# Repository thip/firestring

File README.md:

# FireString

An RP2040-based LED fire simulation controller that drives WS2812B NeoPixel strings to recreate the look of a glowing fireplace.

Full writeup: [davidcapper.dev/posts/fire-string](https://davidcapper.dev/posts/fire-string)

Finished units available at [hortus.dev/products/fire-string](https://hortus.dev/products/fire-string).

## How it works

The simulation is built on three physical concepts:

- **Black-body radiation** — pixel temperatures are mapped to a colour gradient from red (cool) through orange/yellow to white (hot).
- **Heat decay** — each pixel loses a proportion of its heat every frame, fading from bright to dark over time.
- **Thermal diffusion** — pixels transfer heat to neighbours proportionally to temperature difference, so heat spreads naturally through the string.

On top of this, a **fuel system** adds gradual brightness ramps (fuel converts to heat via a burn rate), and **temperature-dependent curves** make cool pixels decay slowly and reignite easily while hot pixels shed heat rapidly — mimicking real ember behaviour.

## Firmware

CircuitPython running on the RP2040 with `@micropython.viper` compilation and integer-only maths for performance. Includes a **web-based configurator** (Web Serial API) for real-time parameter tuning and preset management.

## Hardware

Custom 2-layer RP2040 PCB with USB-C, designed in KiCad. Schematic and board layout are in `hardware/`.

## Licence

- **Hardware** — [CC BY-NC-SA 4.0](hardware/LICENSE)
- **Software** — [MIT](Software/LICENSE)

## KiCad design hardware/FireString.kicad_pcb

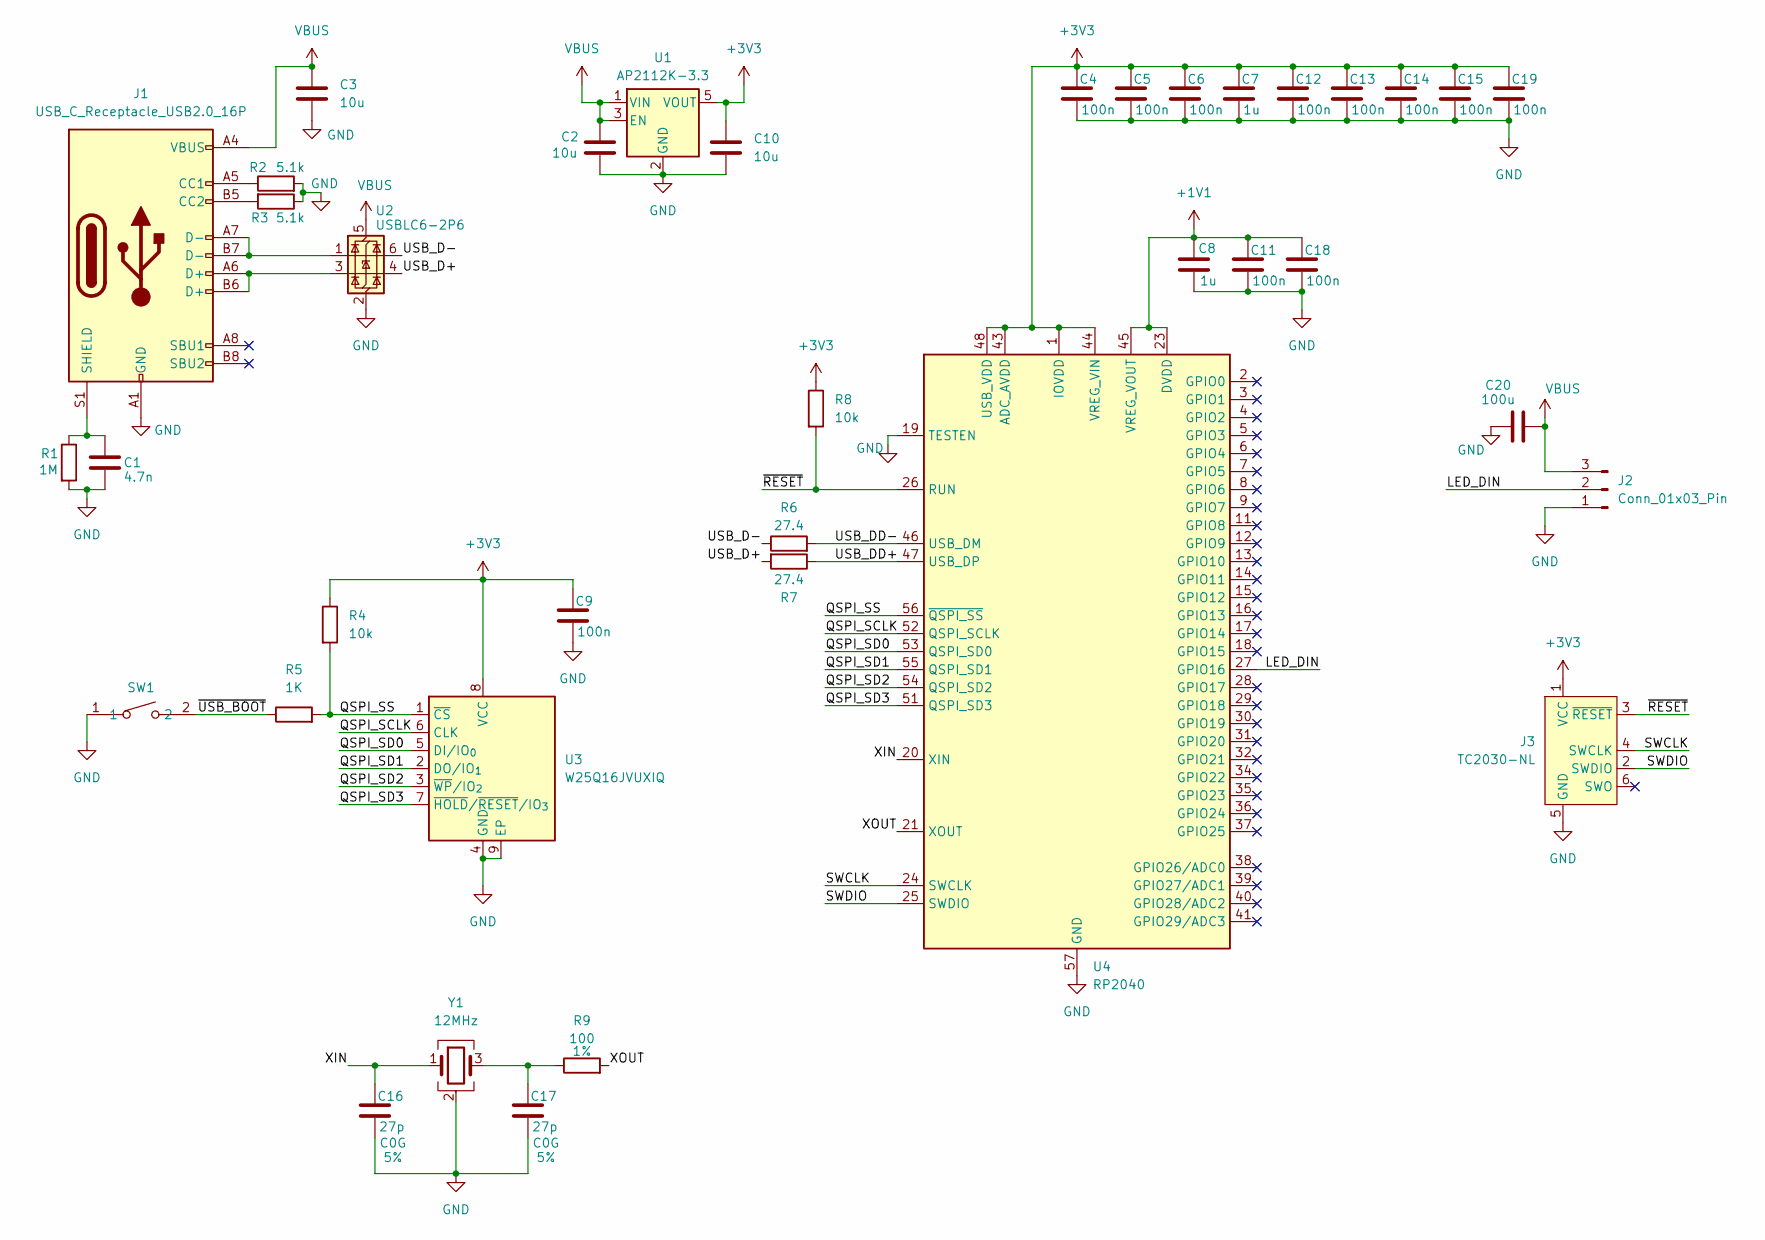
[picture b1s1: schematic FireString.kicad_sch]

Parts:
C1: 4.7n; C_0402_1005Metric
C2, C3, C10: 10u; C_0402_1005Metric
C4, C5, C6, C9, C11, C12, C13, C14, C15, C18, C19: 100n; C_0402_1005Metric
C7, C8: 1u; C_0402_1005Metric
C16, C17: 27p; C_0402_1005Metric; Tolerence 5%
C20: 100u; C_1206_3216Metric
J1: USB_C_Receptacle_USB2.0_16P; USB_C_Receptacle_G-Switch_GT-USB-7010ASV
J2: Conn_01x03_Pin; JST_XH_S3B-XH-A_1x03_P2.50mm_Horizontal
J3: TC2030-NL; Tag-Connect_TC2030-IDC-NL_2x03_P1.27mm_Vertical
R1: 1M; R_0402_1005Metric
R2, R3: 5.1k; R_0402_1005Metric
R4, R8: 10k; R_0402_1005Metric
R5: 1K; R_0402_1005Metric
R6, R7: 27.4; R_0402_1005Metric
R9: 100; R_0402_1005Metric; Tolerence 1%
SW1: SW-SMD_L3.9-W3.0-P4.45
U1: AP2112K-3.3; SOT-23-5
U2: USBLC6-2P6; SOT-666
U3: W25Q16JVUXIQ; USON-8_L3.0-W2.0-P0.50-BL-EP
U4: RP2040; QFN-56-1EP_7x7mm_P0.4mm_EP3.2x3.2mm
Y1: 12MHz; Crystal_SMD_Abracon_ABM8G-4Pin_3.2x2.5mm

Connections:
+1V1: C8.1, C11.1, C18.1, U4.23 (DVDD), U4.45 (VREG_VOUT), U4.50 (DVDD)
+3V3: C4.1, C5.1, C6.1, C7.1, C9.1, C10.1, C12.1, C13.1, C14.1, C15.1, C19.1, J3.1 (VCC), R4.1, R8.1, U1.5 (VOUT), U3.8 (VCC), U4.1 (IOVDD), U4.10 (IOVDD), U4.22 (IOVDD), U4.33 (IOVDD), U4.42 (IOVDD), U4.43 (ADC_AVDD), U4.44 (VREG_VIN), U4.48 (USB_VDD), U4.49 (IOVDD)
/LED_DIN: J2.2, U4.27 (GPIO16)
/QSPI_SCLK: U3.6 (CLK), U4.52 (QSPI_SCLK)
/QSPI_SD0: U3.5 (DI/IO_{0}), U4.53 (QSPI_SD0)
/QSPI_SD1: U3.2 (DO/IO_{1}), U4.55 (QSPI_SD1)
/QSPI_SD2: U3.3 (~WP/IO_{2}), U4.54 (QSPI_SD2)
/QSPI_SD3: U3.7 (~HOLD/~RESET/IO_{3}), U4.51 (QSPI_SD3)
/QSPI_SS: R4.2, R5.2, U3.1 (~CS), U4.56 (~QSPI_SS)
/SWCLK: J3.4 (SWCLK), U4.24 (SWCLK)
/SWDIO: J3.2 (SWDIO), U4.25 (SWDIO)
/USB_D+: R7.2, U2.4 (I/O2)
/USB_D-: R6.1, U2.6 (I/O1)
/USB_DD+: R7.1, U4.47 (USB_DP)
/USB_DD-: R6.2, U4.46 (USB_DM)
/XIN: C16.1, U4.20 (XIN), Y1.1
/XOUT: R9.2, U4.21 (XOUT)
/~RESET: J3.3 (~RESET), R8.2, U4.26 (RUN)
/~USB_BOOT: R5.1, SW1.2
GND: C1.2, C2.2, C3.1, C4.2, C5.2, C6.2, C7.2, C8.2, C9.2, C10.2, C11.2, C12.2, C13.2, C14.2, C15.2, C16.2, C17.2, C18.2, C19.2, C20.1, J1.A1 (GND), J1.A12 (GND), J1.B1 (GND), J1.B12 (GND), J2.1, J3.5 (GND), R1.2, R2.2, R3.1, SW1.1, U1.2 (GND), U2.2 (GND), U3.4 (GND), U3.9 (EP), U4.19 (TESTEN), U4.57 (GND), Y1.2 (G), Y1.4 (G)
unnamed: C17.1, R9.1, Y1.3
unnamed: J1.A5 (CC1), R2.1
unnamed: J1.B5 (CC2), R3.2
unnamed: J1.A6 (D+), J1.B6 (D+), U2.3 (I/O2)
unnamed: J1.A7 (D-), J1.B7 (D-), U2.1 (I/O1)
unnamed: C1.1, J1.S1 (SHIELD), R1.1
VBUS: C2.1, C3.2, C20.2, J1.A4 (VBUS), J1.A9 (VBUS), J1.B4 (VBUS), J1.B9 (VBUS), J2.3, U1.1 (VIN), U1.3 (EN), U2.5 (VBUS)

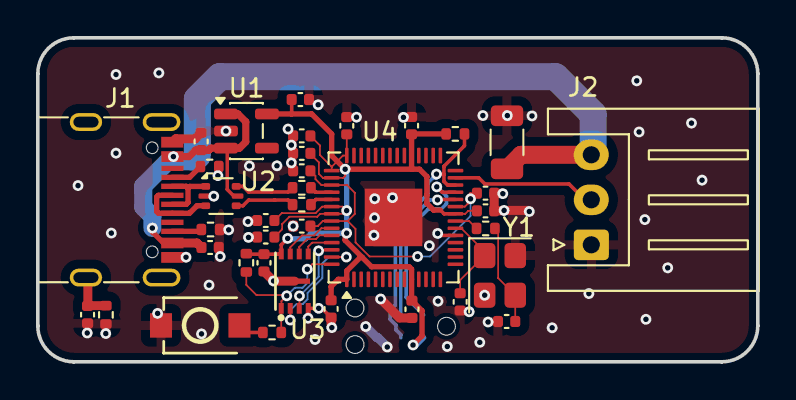
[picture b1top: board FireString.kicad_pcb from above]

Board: 2 copper layers, 40.0 x 18.0 mm, 38 parts (1 on the bottom side), 27 nets.

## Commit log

2026-03-29 Initial commit: FireString hardware and firmware
    Public release with hardware design files (KiCad) and CircuitPython
    firmware. Hardware licensed CC BY-NC-SA 4.0, software licensed MIT.
